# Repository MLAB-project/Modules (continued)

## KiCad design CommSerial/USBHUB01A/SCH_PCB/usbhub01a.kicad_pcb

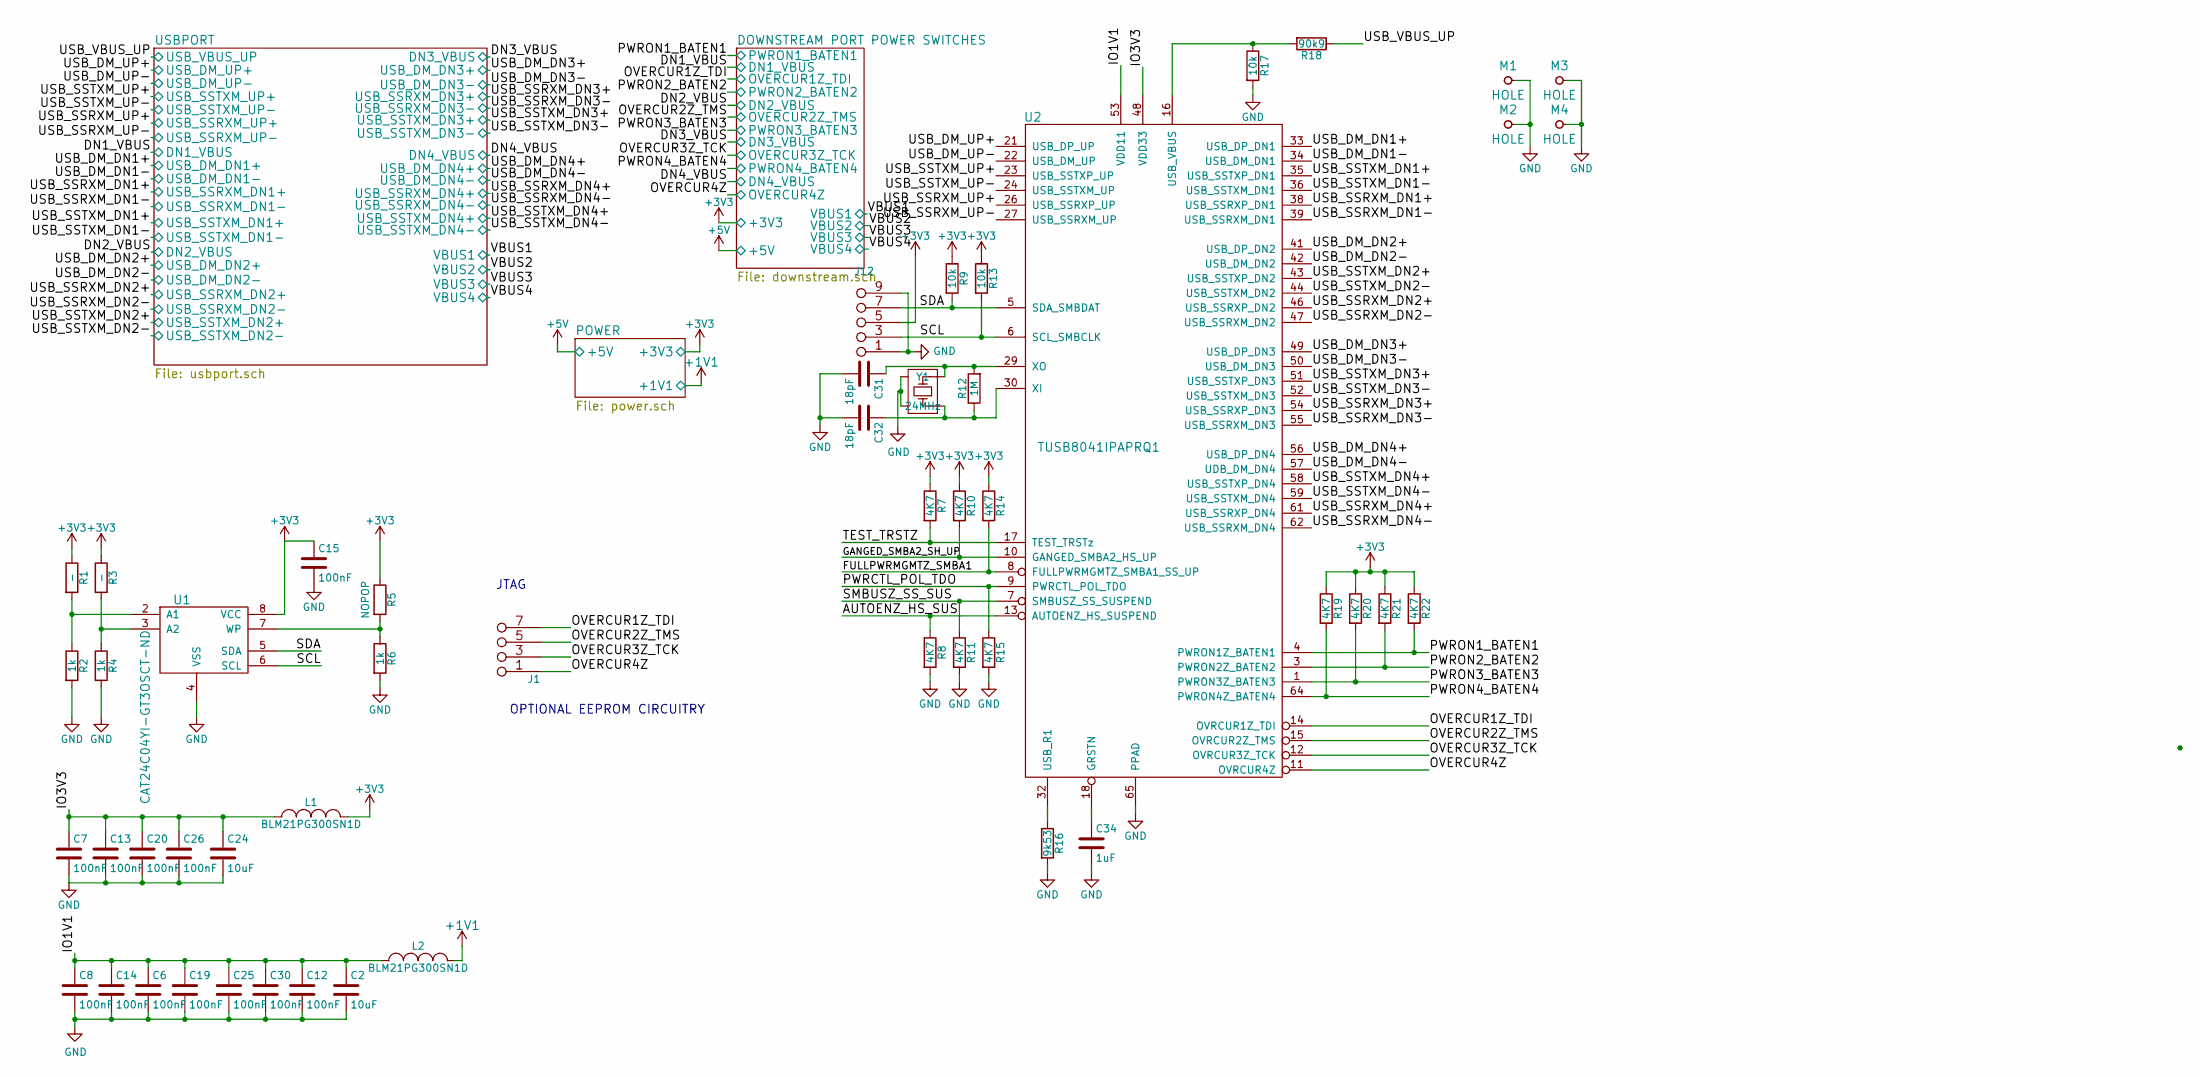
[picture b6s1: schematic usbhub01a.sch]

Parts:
C2, C24: 10uF; SMD-0805
C6, C7, C8, C12, C13, C14, C15, C19, C20, C25, C26, C30: 100nF; SMD-0603
C31, C32: 18pF; SMD-0603
C34: 1uF; SMD-0603
J1: JUMP_2x1; Straight_2x04
J12: JUMP_5X2; Straight_2x05
L1, L2: BLM21PG300SN1D; SMD-0805
M1, M2, M3, M4: HOLE; MountingHole_3mm
R1, R3: -; SMD-0603
R2, R4, R6: 1k; SMD-0603
R5: NOPOP; SMD-0603
R7, R8, R10, R11, R14, R15, R19, R20, R21, R22: 4K7; SMD-0603
R9, R13, R17: 10k; SMD-0603
R12: 1M; SMD-0603
R16: 9k53; SMD-0603
R18: 90k9; SMD-0603
U1: CAT24C04YI-GT3OSCT-ND; TSSOP-8_4.4x3mm_Pitch0.65mm
U2: TUSB8041IPAPRQ1; HTQFP-64_10x10mm_Pitch0.5mm
Y1: 24MHz; NX2016HA

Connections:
+1V1: L2.2; also elsewhere on the board
+3V3: C15.1, J12.5 (6), J12.6, L1.2, R1.1, R3.1, R5.1, R7.1, R9.1, R10.1, R13.1, R14.1, R19.1, R20.1, R21.1, R22.1, U1.8 (VCC); also elsewhere on the board
/AUTOENZ_HS_SUS: R8.1, U2.13 (AUTOENZ_HS_SUSPEND); also elsewhere on the board
/FULLPWRMGMTZ_SMBA1: R14.2, U2.8 (FULLPWRMGMTZ_SMBA1_SS_UP); also elsewhere on the board
/GANGED_SMBA2_SH_UP: R10.2, U2.10 (GANGED_SMBA2_HS_UP); also elsewhere on the board
/IO1V1: C2.1, C6.1, C8.1, C12.1, C14.1, C19.1, C25.1, C30.1, L2.1, U2.19 (VDD11), U2.25 (VDD11), U2.37 (VDD11), U2.45 (VDD11), U2.53 (VDD11), U2.60 (VDD11), U2.63 (VDD11)
/IO3V3: C7.1, C13.1, C20.1, C24.1, C26.1, L1.1, U2.2 (VDD33), U2.20 (VDD33), U2.31 (VDD33), U2.48 (VDD33)
/OVERCUR1Z_TDI: J1.7 (8), J1.8, U2.14 (OVRCUR1Z_TDI); also elsewhere on the board
/OVERCUR2Z_TMS: J1.5, J1.6 (5), U2.15 (OVRCUR2Z_TMS); also elsewhere on the board
/OVERCUR3Z_TCK: J1.3 (4), J1.4, U2.12 (OVRCUR3Z_TCK); also elsewhere on the board
/OVERCUR4Z: J1.1 (2), J1.2, U2.11 (OVRCUR4Z); also elsewhere on the board
/PWRCTL_POL_TDO: R15.1, U2.9 (PWRCTL_POL_TDO); also elsewhere on the board
/PWRON1_BATEN1: R22.2, U2.4 (PWRON1Z_BATEN1); also elsewhere on the board
/PWRON2_BATEN2: R21.2, U2.3 (PWRON2Z_BATEN2); also elsewhere on the board
/PWRON3_BATEN3: R20.2, U2.1 (PWRON3Z_BATEN3); also elsewhere on the board
/PWRON4_BATEN4: R19.2, U2.64 (PWRON4Z_BATEN4); also elsewhere on the board
/SCL: J12.3 (4), J12.4, R13.2, U1.6 (SCL), U2.6 (SCL_SMBCLK)
/SDA: J12.7, J12.8 (7), R9.2, U1.5 (SDA), U2.5 (SDA_SMBDAT)
/SMBUSZ_SS_SUS: R11.1, U2.7 (SMBUSZ_SS_SUSPEND); also elsewhere on the board
/TEST_TRSTZ: R7.2, U2.17 (TEST_TRSTz); also elsewhere on the board
/USB_DM_DN1+: U2.33 (USB_DP_DN1); also elsewhere on the board
/USB_DM_DN1-: U2.34 (USB_DM_DN1); also elsewhere on the board
/USB_DM_DN2+: U2.41 (USB_DP_DN2); also elsewhere on the board
/USB_DM_DN2-: U2.42 (USB_DM_DN2); also elsewhere on the board
/USB_DM_DN3+: U2.49 (USB_DP_DN3); also elsewhere on the board
/USB_DM_DN3-: U2.50 (USB_DM_DN3); also elsewhere on the board
/USB_DM_DN4+: U2.56 (USB_DP_DN4); also elsewhere on the board
/USB_DM_DN4-: U2.57 (UDB_DM_DN4); also elsewhere on the board
/USB_DM_UP+: U2.21 (USB_DP_UP); also elsewhere on the board
/USB_DM_UP-: U2.22 (USB_DM_UP); also elsewhere on the board
/USB_SSRXM_DN1+: U2.38 (USB_SSRXP_DN1); also elsewhere on the board
/USB_SSRXM_DN1-: U2.39 (USB_SSRXM_DN1); also elsewhere on the board
/USB_SSRXM_DN2+: U2.46 (USB_SSRXP_DN2); also elsewhere on the board
/USB_SSRXM_DN2-: U2.47 (USB_SSRXM_DN2); also elsewhere on the board
/USB_SSRXM_DN3+: U2.54 (USB_SSRXP_DN3); also elsewhere on the board
/USB_SSRXM_DN3-: U2.55 (USB_SSRXM_DN3); also elsewhere on the board
/USB_SSRXM_DN4+: U2.61 (USB_SSRXP_DN4); also elsewhere on the board
/USB_SSRXM_DN4-: U2.62 (USB_SSRXM_DN4); also elsewhere on the board
/USB_SSRXM_UP+: U2.26 (USB_SSRXP_UP); also elsewhere on the board
/USB_SSRXM_UP-: U2.27 (USB_SSRXM_UP); also elsewhere on the board
/USB_SSTXM_DN1+: U2.35 (USB_SSTXP_DN1); also elsewhere on the board
/USB_SSTXM_DN1-: U2.36 (USB_SSTXM_DN1); also elsewhere on the board
/USB_SSTXM_DN2+: U2.43 (USB_SSTXP_DN2); also elsewhere on the board
/USB_SSTXM_DN2-: U2.44 (USB_SSTXM_DN2); also elsewhere on the board
/USB_SSTXM_DN3+: U2.51 (USB_SSTXP_DN3); also elsewhere on the board
/USB_SSTXM_DN3-: U2.52 (USB_SSTXM_DN3); also elsewhere on the board
/USB_SSTXM_DN4+: U2.58 (USB_SSTXP_DN4); also elsewhere on the board
/USB_SSTXM_DN4-: U2.59 (USB_SSTXM_DN4); also elsewhere on the board
/USB_SSTXM_UP+: U2.23 (USB_SSTXP_UP); also elsewhere on the board
/USB_SSTXM_UP-: U2.24 (USB_SSTXM_UP); also elsewhere on the board
/USB_VBUS_UP: R18.1; also elsewhere on the board
GND: C2.2, C6.2, C7.2, C8.2, C12.2, C13.2, C14.2, C15.2, C19.2, C20.2, C24.2, C25.2, C26.2, C30.2, C31.2, C32.2, C34.2, J12.1 (2), J12.2, J12.9 (10), J12.10, M1.1, M2.1, M3.1, M4.1, R2.2, R4.2, R6.2, R8.2, R11.2, R15.2, R16.2, R17.2, U1.4 (VSS), U2.65 (PPAD), Y1.2, Y1.4; also elsewhere on the board
unnamed: C31.1, R12.2, U2.29 (XO), Y1.3
unnamed: C32.1, R12.1, U2.30 (XI), Y1.1
unnamed: C34.1, U2.18 (GRSTN)
unnamed: R1.2, R2.1, U1.2 (A1)
unnamed: R3.2, R4.1, U1.3 (A2)
unnamed: R5.2, R6.1, U1.7 (WP)
unnamed: R16.1, U2.32 (USB_R1)
unnamed: R17.1, R18.2, U2.16 (USB_VBUS)

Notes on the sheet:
OPTIONAL EEPROM CIRCUITRY
JTAG

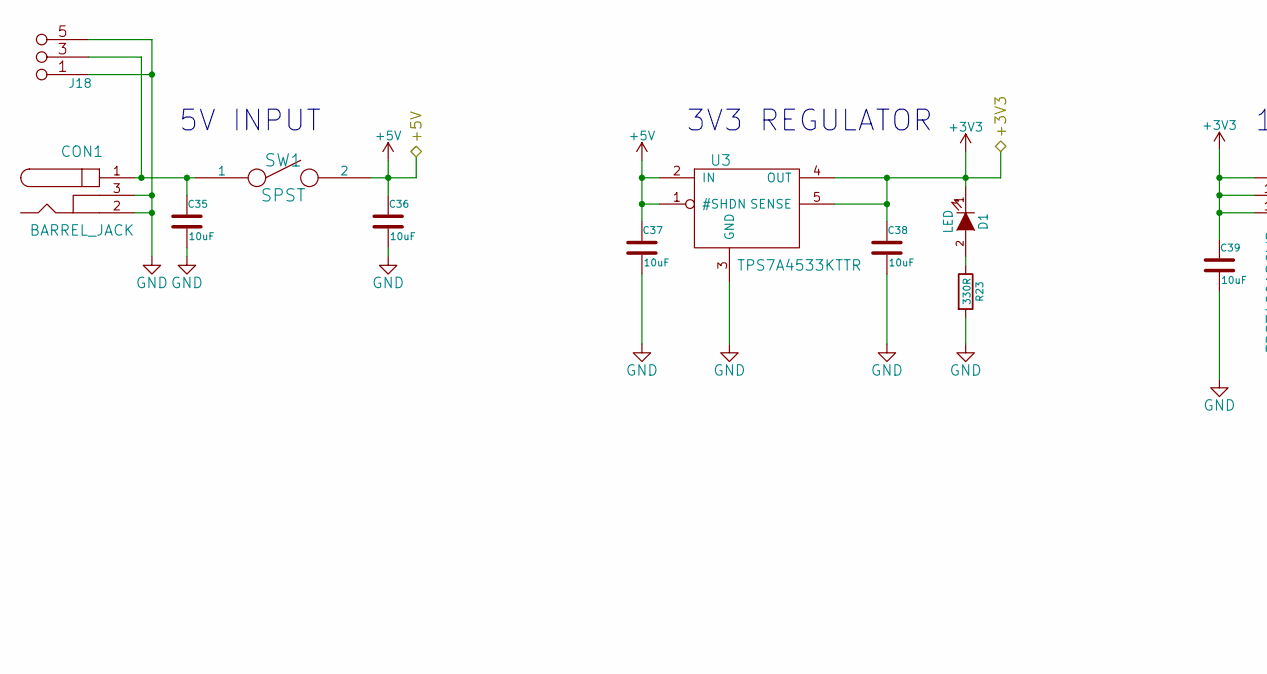
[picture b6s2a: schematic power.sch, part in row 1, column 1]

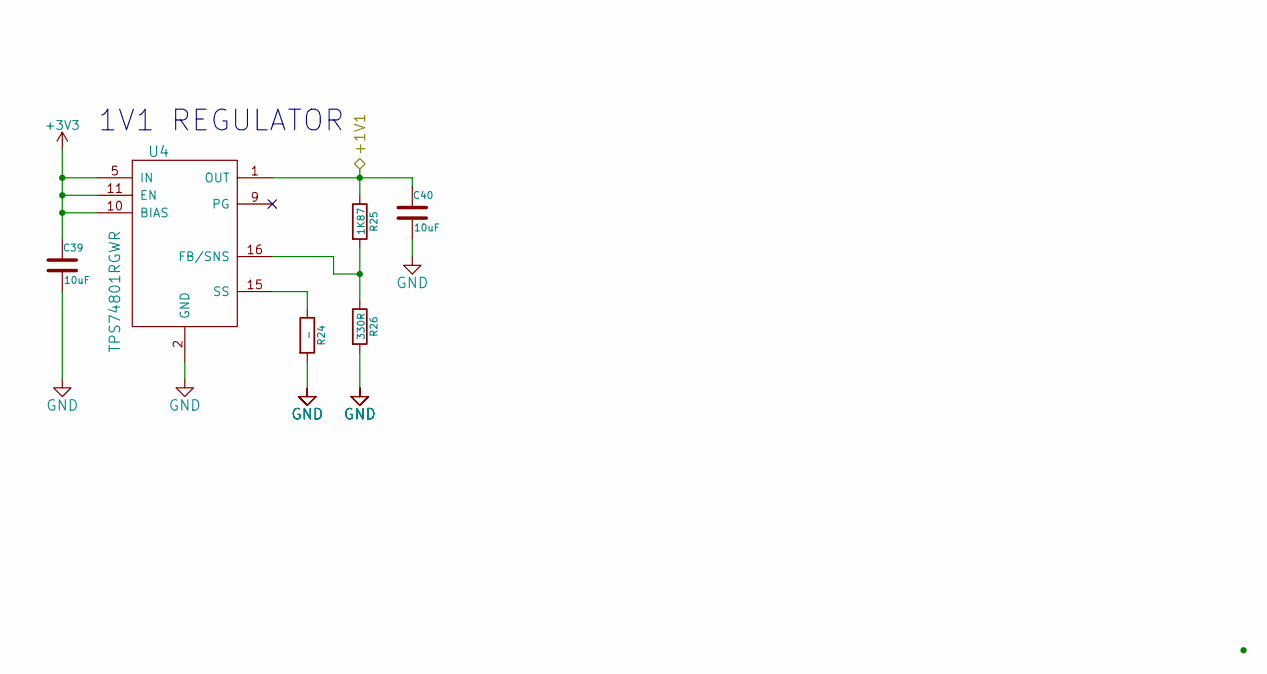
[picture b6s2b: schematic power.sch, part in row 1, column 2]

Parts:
C35, C36, C37, C38, C39, C40: 10uF; SMD-0805
CON1: BARREL_JACK; DC2,1MM
D1: LED; LED_1206
J18: JUMP_3X2; Straight_2x03
R23, R26: 330R; SMD-0603
R24: -; SMD-0603
R25: 1K87; SMD-0603
SW1: SPST; Prepinaci_3A_SL19121
U3: TPS7A4533KTTR; TO-263-5
U4: TPS74801RGWR; QFN-20-1EP_5x5mm_Pitch0.65mm

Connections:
+1V1: C40.1, R25.1, U4.1 (OUT), U4.18 (OUT), U4.19 (OUT), U4.20 (OUT); also elsewhere on the board
+3V3: C38.1, C39.1, D1.1 (K), U3.4 (OUT), U3.5 (SENSE), U4.5 (IN), U4.6 (IN), U4.7 (IN), U4.8 (IN), U4.10 (BIAS), U4.11 (EN); also elsewhere on the board
+5V: C36.1, C37.1, SW1.2, U3.1 (#SHDN), U3.2 (IN); also elsewhere on the board
GND: C35.2, C36.2, C37.2, C38.2, C39.2, C40.2, CON1.2, CON1.3, J18.1 (2), J18.2, J18.5 (6), J18.6, R23.2, R24.2, R26.2, U3.3 (GND), U3.6 (GND), U4.2 (GND), U4.3 (GND), U4.4 (GND), U4.12 (GND), U4.13 (GND), U4.14 (GND), U4.21; also elsewhere on the board
unnamed: C35.1, CON1.1, J18.3 (4), J18.4, SW1.1
unnamed: D1.2 (A), R23.1
unnamed: R24.1, U4.15 (SS)
unnamed: R25.2, R26.1, U4.16 (FB/SNS)

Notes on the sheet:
5V INPUT
3V3 REGULATOR
1V1 REGULATOR

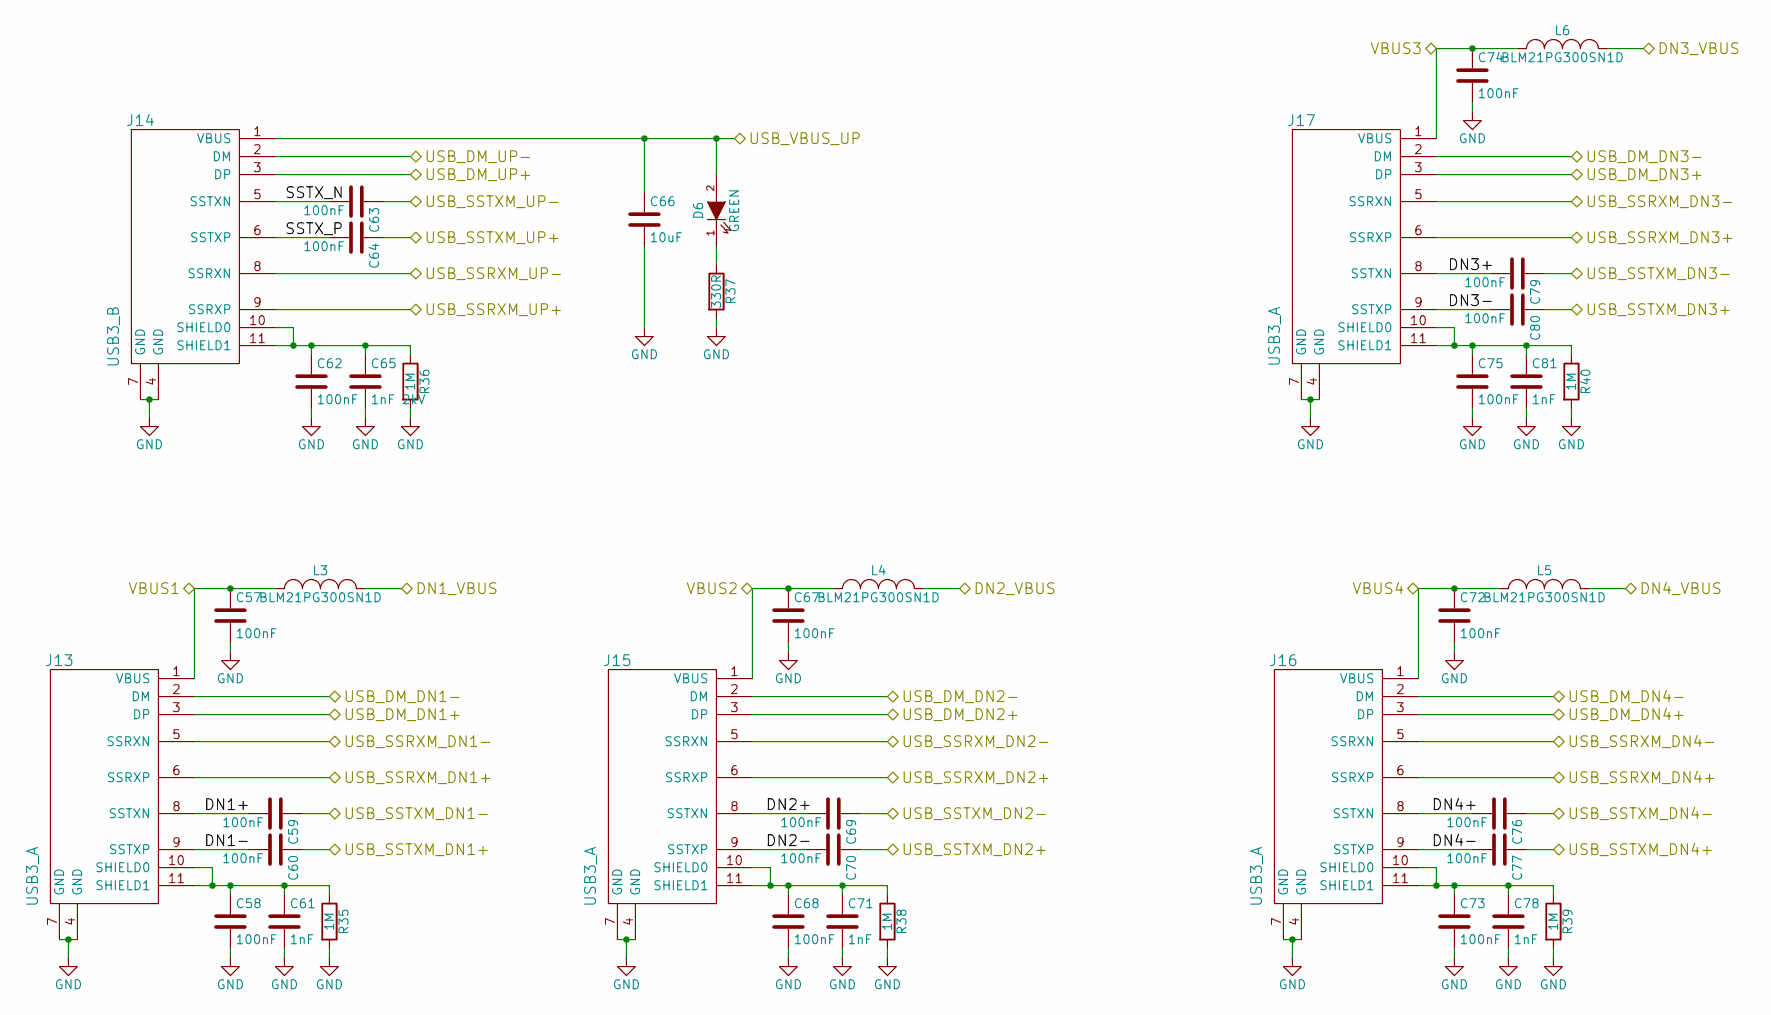
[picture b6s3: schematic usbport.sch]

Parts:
C57, C58, C59, C60, C62, C63, C64, C67, C68, C69, C70, C72, C73, C74, C75, C76, C77, C79, C80: 100nF; SMD-0603
C61, C71, C78, C81: 1nF; SMD-0603
C65: 1nF 2kV; SMD-0603
C66: 10uF; SMD-0603
D6: GREEN; LED_1206
J13, J15, J16, J17: USB3_A; USB3_0_A
J14: USB3_B; USB3_0_B
L3, L4, L5, L6: BLM21PG300SN1D; SMD-0805
R35, R36, R38, R39, R40: 1M; SMD-0603
R37: 330R; SMD-0603

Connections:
/DN1_VBUS: L3.2; also elsewhere on the board
/DN2_VBUS: L4.2; also elsewhere on the board
/DN3_VBUS: L6.2; also elsewhere on the board
/DN4_VBUS: L5.2; also elsewhere on the board
/USBPORT/DN1+: C59.2, J13.8 (SSTXN)
/USBPORT/DN1-: C60.2, J13.9 (SSTXP)
/USBPORT/DN2+: C69.2, J15.8 (SSTXN)
/USBPORT/DN2-: C70.2, J15.9 (SSTXP)
/USBPORT/DN3+: C79.2, J17.8 (SSTXN)
/USBPORT/DN3-: C80.2, J17.9 (SSTXP)
/USBPORT/DN4+: C76.2, J16.8 (SSTXN)
/USBPORT/DN4-: C77.2, J16.9 (SSTXP)
/USBPORT/SSTX_N: C63.2, J14.5 (SSTXN)
/USBPORT/SSTX_P: C64.2, J14.6 (SSTXP)
/USB_DM_DN1+: J13.3 (DP); also elsewhere on the board
/USB_DM_DN1-: J13.2 (DM); also elsewhere on the board
/USB_DM_DN2+: J15.3 (DP); also elsewhere on the board
/USB_DM_DN2-: J15.2 (DM); also elsewhere on the board
/USB_DM_DN3+: J17.3 (DP); also elsewhere on the board
/USB_DM_DN3-: J17.2 (DM); also elsewhere on the board
/USB_DM_DN4+: J16.3 (DP); also elsewhere on the board
/USB_DM_DN4-: J16.2 (DM); also elsewhere on the board
/USB_DM_UP+: J14.3 (DP); also elsewhere on the board
/USB_DM_UP-: J14.2 (DM); also elsewhere on the board
/USB_SSRXM_DN1+: J13.6 (SSRXP); also elsewhere on the board
/USB_SSRXM_DN1-: J13.5 (SSRXN); also elsewhere on the board
/USB_SSRXM_DN2+: J15.6 (SSRXP); also elsewhere on the board
/USB_SSRXM_DN2-: J15.5 (SSRXN); also elsewhere on the board
/USB_SSRXM_DN3+: J17.6 (SSRXP); also elsewhere on the board
/USB_SSRXM_DN3-: J17.5 (SSRXN); also elsewhere on the board
/USB_SSRXM_DN4+: J16.6 (SSRXP); also elsewhere on the board
/USB_SSRXM_DN4-: J16.5 (SSRXN); also elsewhere on the board
/USB_SSRXM_UP+: J14.9 (SSRXP); also elsewhere on the board
/USB_SSRXM_UP-: J14.8 (SSRXN); also elsewhere on the board
/USB_SSTXM_DN1+: C60.1; also elsewhere on the board
/USB_SSTXM_DN1-: C59.1; also elsewhere on the board
/USB_SSTXM_DN2+: C70.1; also elsewhere on the board
/USB_SSTXM_DN2-: C69.1; also elsewhere on the board
/USB_SSTXM_DN3+: C80.1; also elsewhere on the board
/USB_SSTXM_DN3-: C79.1; also elsewhere on the board
/USB_SSTXM_DN4+: C77.1; also elsewhere on the board
/USB_SSTXM_DN4-: C76.1; also elsewhere on the board
/USB_SSTXM_UP+: C64.1; also elsewhere on the board
/USB_SSTXM_UP-: C63.1; also elsewhere on the board
/USB_VBUS_UP: C66.1, D6.2 (A), J14.1 (VBUS); also elsewhere on the board
/VBUS1: C57.1, J13.1 (VBUS), L3.1; also elsewhere on the board
/VBUS2: C67.1, J15.1 (VBUS), L4.1; also elsewhere on the board
/VBUS3: C74.1, J17.1 (VBUS), L6.1; also elsewhere on the board
/VBUS4: C72.1, J16.1 (VBUS), L5.1; also elsewhere on the board
GND: C57.2, C58.2, C61.2, C62.2, C65.2, C66.2, C67.2, C68.2, C71.2, C72.2, C73.2, C74.2, C75.2, C78.2, C81.2, J13.4 (GND), J13.7 (GND), J14.4 (GND), J14.7 (GND), J15.4 (GND), J15.7 (GND), J16.4 (GND), J16.7 (GND), J17.4 (GND), J17.7 (GND), R35.2, R36.2, R37.2, R38.2, R39.2, R40.2; also elsewhere on the board
unnamed: C58.1, C61.1, J13.10 (SHIELD0), J13.11 (SHIELD1), R35.1
unnamed: C62.1, C65.1, J14.10 (SHIELD0), J14.11 (SHIELD1), R36.1
unnamed: C68.1, C71.1, J15.10 (SHIELD0), J15.11 (SHIELD1), R38.1
unnamed: C73.1, C78.1, J16.10 (SHIELD0), J16.11 (SHIELD1), R39.1
unnamed: C75.1, C81.1, J17.10 (SHIELD0), J17.11 (SHIELD1), R40.1
unnamed: D6.1 (K), R37.1

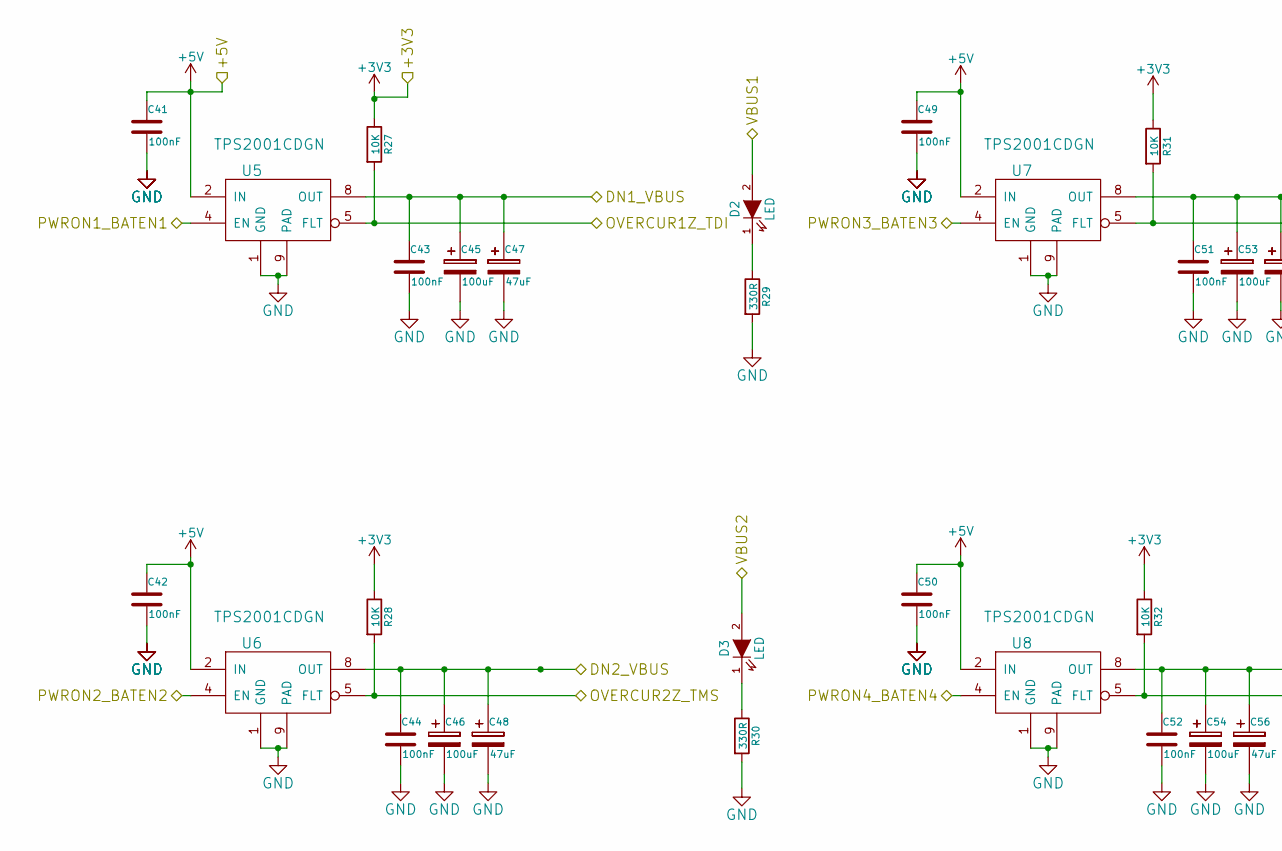
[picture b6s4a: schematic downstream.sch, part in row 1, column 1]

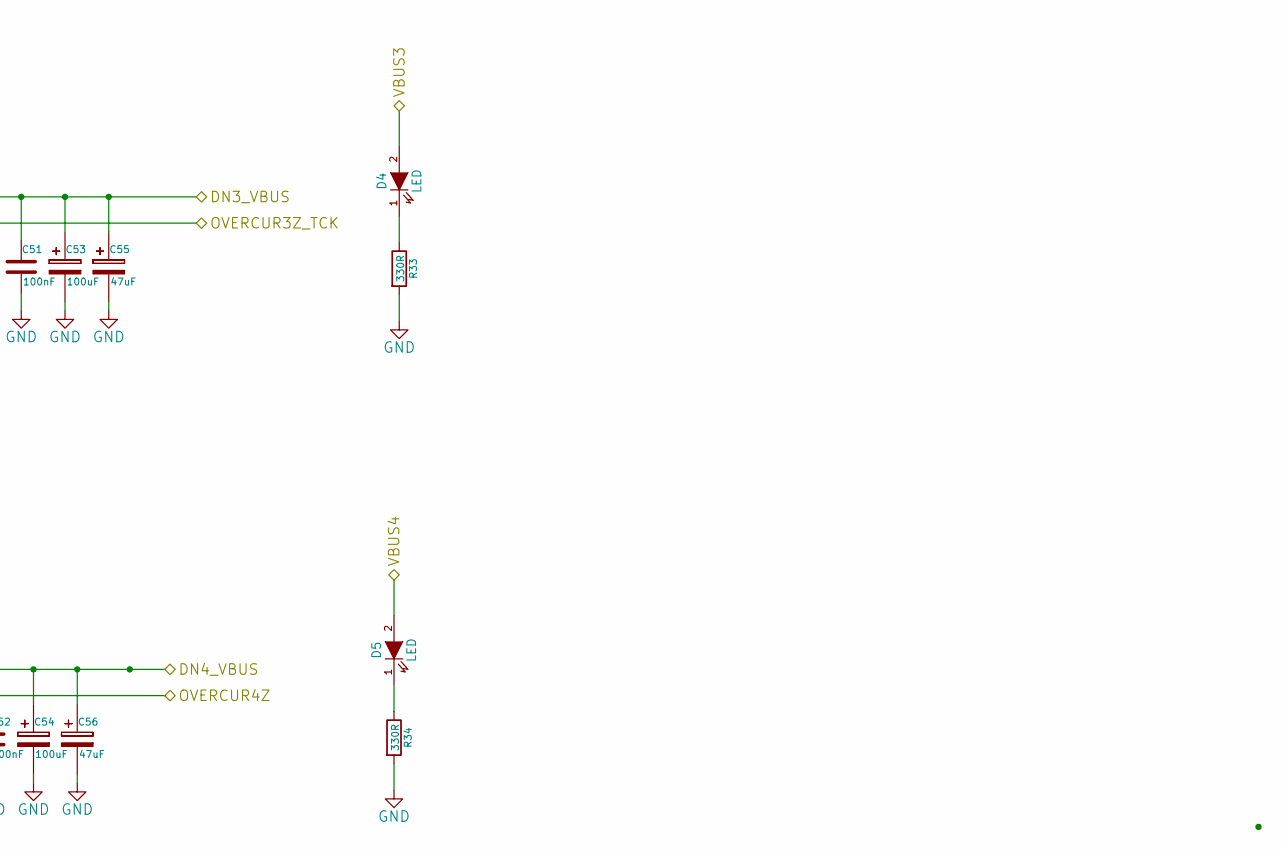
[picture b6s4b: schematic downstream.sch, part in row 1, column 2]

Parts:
C41, C42, C43, C44, C49, C50, C51, C52: 100nF; SMD-0603
C45, C46, C53, C54: 100uF; TantalC_SizeD_Reflow
C47, C48, C55, C56: 47uF; TantalC_SizeC_Reflow
D2, D3, D4, D5: LED; LED_1206
R27, R28, R31, R32: 10K; SMD-0603
R29, R30, R33, R34: 330R; SMD-0603
U5, U6, U7, U8: TPS2001CDGN; MSOP-8-1EP_3x3mm_Pitch0.65mm

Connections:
+3V3: R27.1, R28.1, R31.1, R32.1; also elsewhere on the board
+5V: C41.1, C42.1, C49.1, C50.1, U5.2 (IN), U5.3 (IN), U6.2 (IN), U6.3 (IN), U7.2 (IN), U7.3 (IN), U8.2 (IN), U8.3 (IN); also elsewhere on the board
/DN1_VBUS: C43.1, C45.1, C47.1, U5.6 (OUT), U5.7 (OUT), U5.8 (OUT); also elsewhere on the board
/DN2_VBUS: C44.1, C46.1, C48.1, U6.6 (OUT), U6.7 (OUT), U6.8 (OUT); also elsewhere on the board
/DN3_VBUS: C51.1, C53.1, C55.1, U7.6 (OUT), U7.7 (OUT), U7.8 (OUT); also elsewhere on the board
/DN4_VBUS: C52.1, C54.1, C56.1, U8.6 (OUT), U8.7 (OUT), U8.8 (OUT); also elsewhere on the board
/OVERCUR1Z_TDI: R27.2, U5.5 (FLT); also elsewhere on the board
/OVERCUR2Z_TMS: R28.2, U6.5 (FLT); also elsewhere on the board
/OVERCUR3Z_TCK: R31.2, U7.5 (FLT); also elsewhere on the board
/OVERCUR4Z: R32.2, U8.5 (FLT); also elsewhere on the board
/PWRON1_BATEN1: U5.4 (EN); also elsewhere on the board
/PWRON2_BATEN2: U6.4 (EN); also elsewhere on the board
/PWRON3_BATEN3: U7.4 (EN); also elsewhere on the board
/PWRON4_BATEN4: U8.4 (EN); also elsewhere on the board
/VBUS1: D2.2 (A); also elsewhere on the board
/VBUS2: D3.2 (A); also elsewhere on the board
/VBUS3: D4.2 (A); also elsewhere on the board
/VBUS4: D5.2 (A); also elsewhere on the board
GND: C41.2, C42.2, C43.2, C44.2, C45.2, C46.2, C47.2, C48.2, C49.2, C50.2, C51.2, C52.2, C53.2, C54.2, C55.2, C56.2, R29.2, R30.2, R33.2, R34.2, U5.1 (GND), U5.9 (PAD), U6.1 (GND), U6.9 (PAD), U7.1 (GND), U7.9 (PAD), U8.1 (GND), U8.9 (PAD); also elsewhere on the board
unnamed: D2.1 (K), R29.1
unnamed: D3.1 (K), R30.1
unnamed: D4.1 (K), R33.1
unnamed: D5.1 (K), R34.1

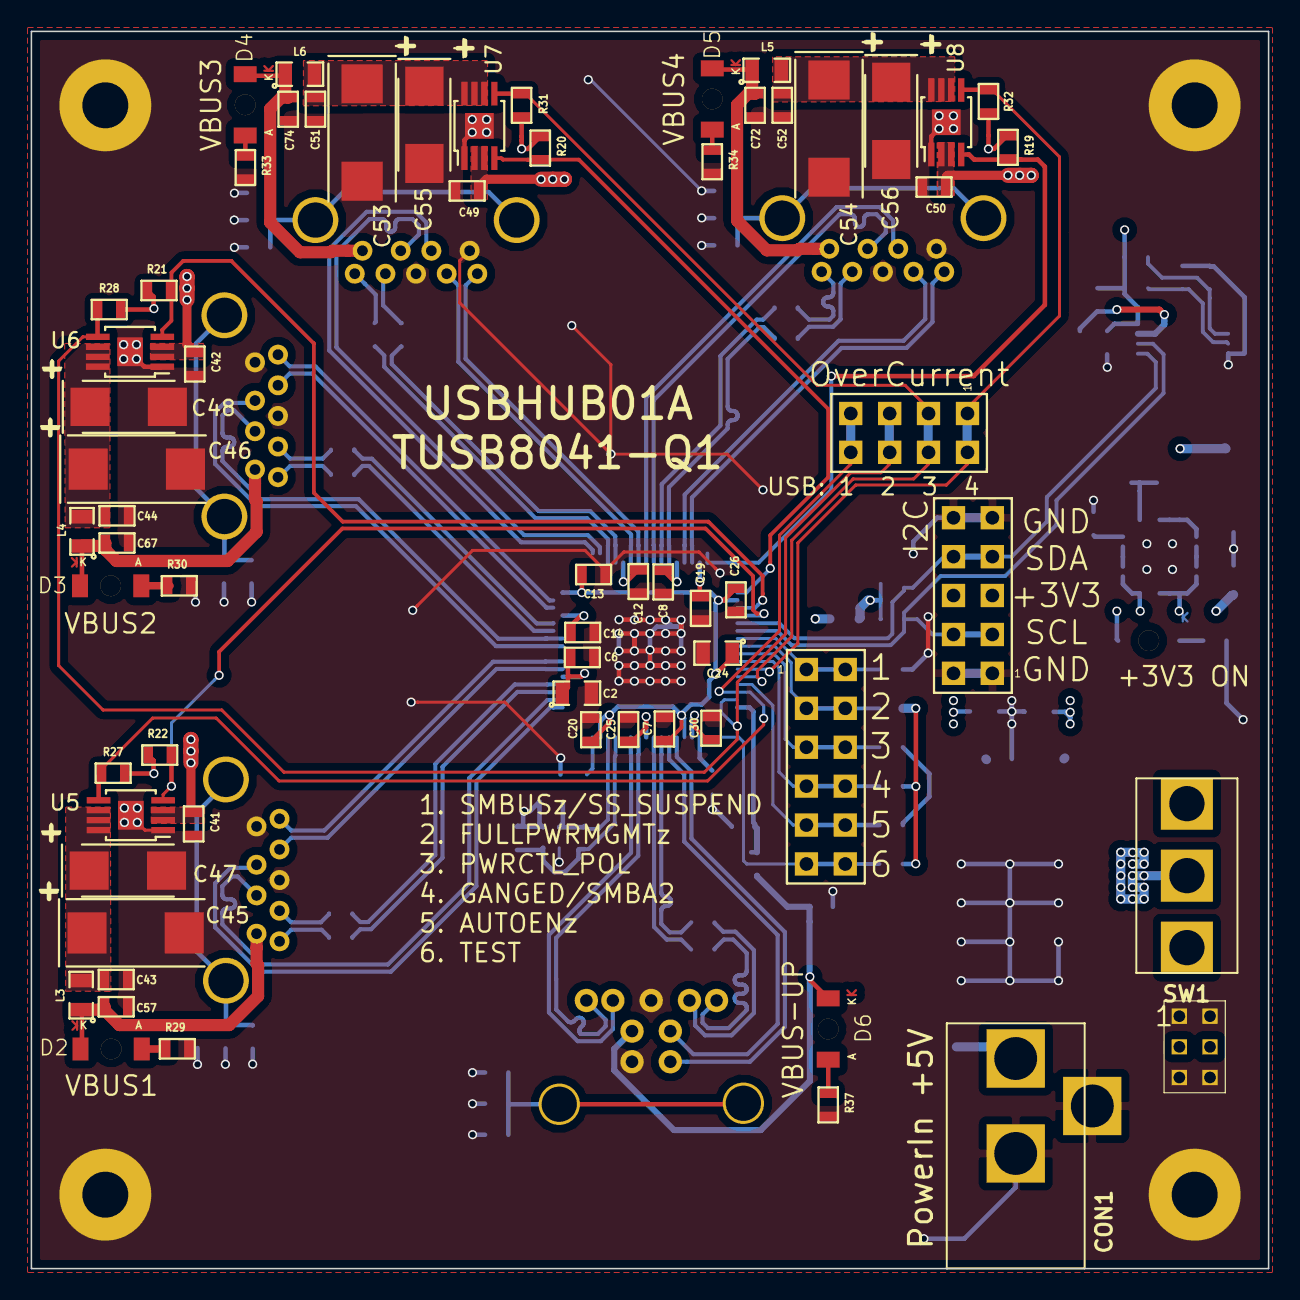
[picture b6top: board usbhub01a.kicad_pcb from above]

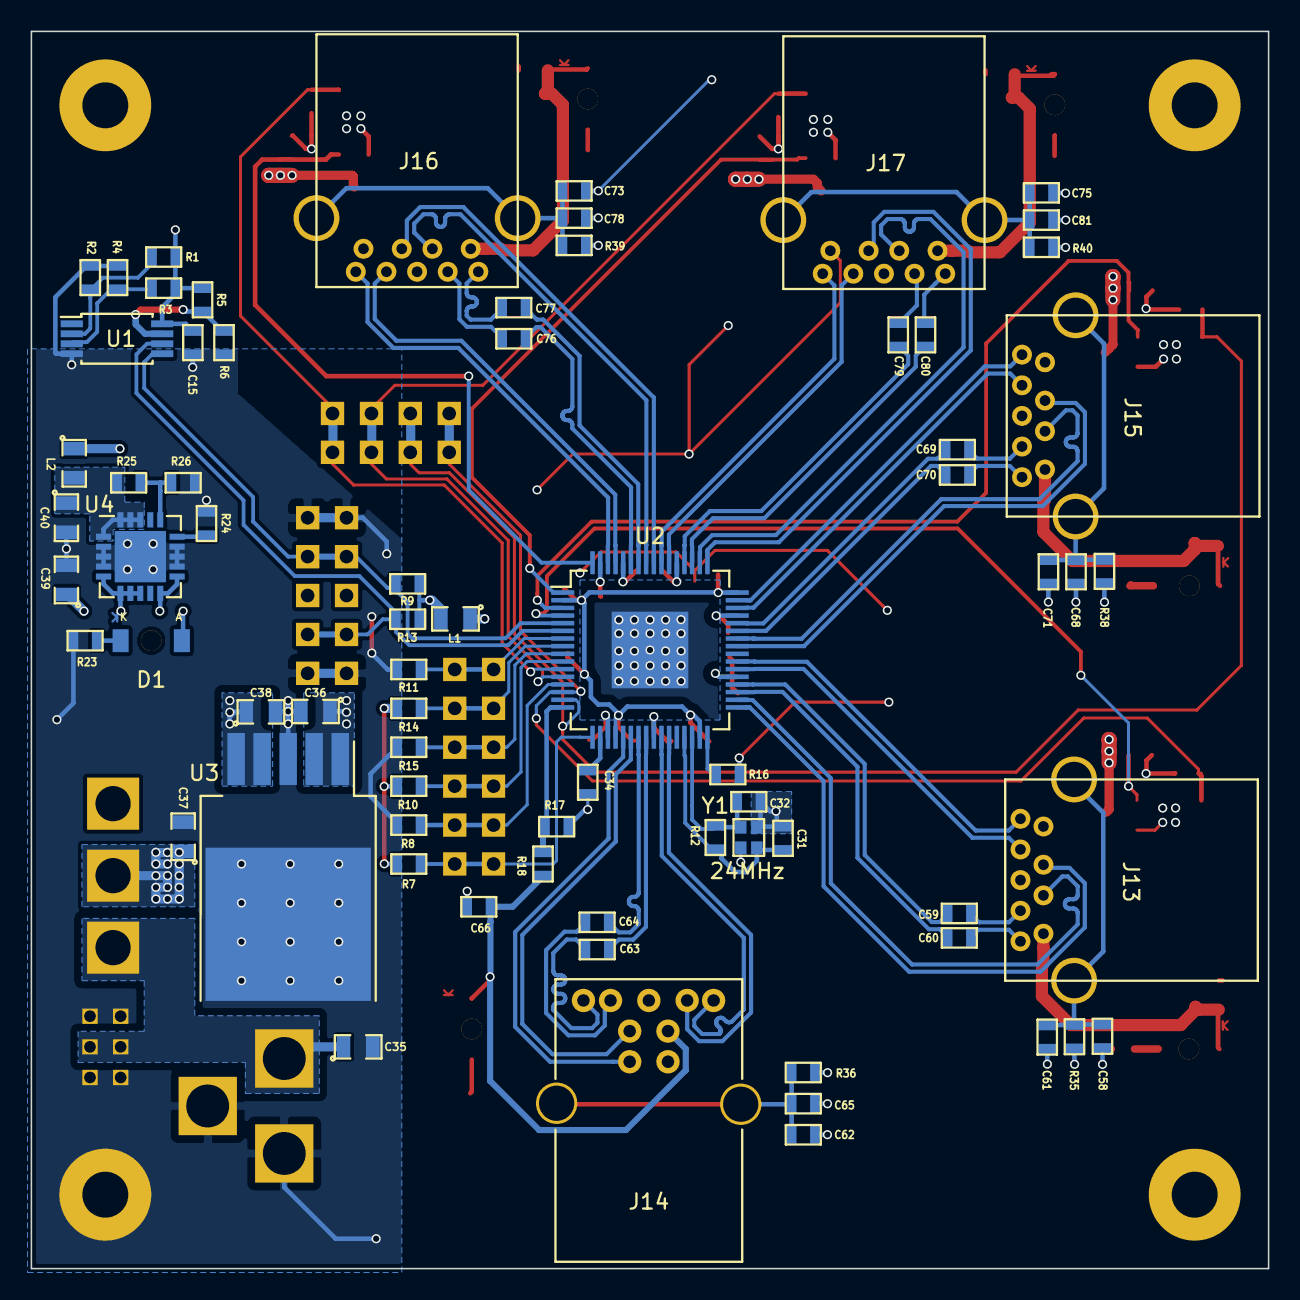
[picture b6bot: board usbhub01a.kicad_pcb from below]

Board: 4 copper layers, 80.8 x 80.8 mm, 140 parts (71 on the bottom side), 93 nets.

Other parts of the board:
J2: Test & Misc Signals; Straight_2x06

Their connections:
/AUTOENZ_HS_SUS: J2.9, J2.10; also elsewhere on the board
/FULLPWRMGMTZ_SMBA1: J2.3, J2.4; also elsewhere on the board
/GANGED_SMBA2_SH_UP: J2.7, J2.8; also elsewhere on the board
/PWRCTL_POL_TDO: J2.5, J2.6; also elsewhere on the board
/SMBUSZ_SS_SUS: J2.1, J2.2; also elsewhere on the board
/TEST_TRSTZ: J2.11, J2.12; also elsewhere on the board

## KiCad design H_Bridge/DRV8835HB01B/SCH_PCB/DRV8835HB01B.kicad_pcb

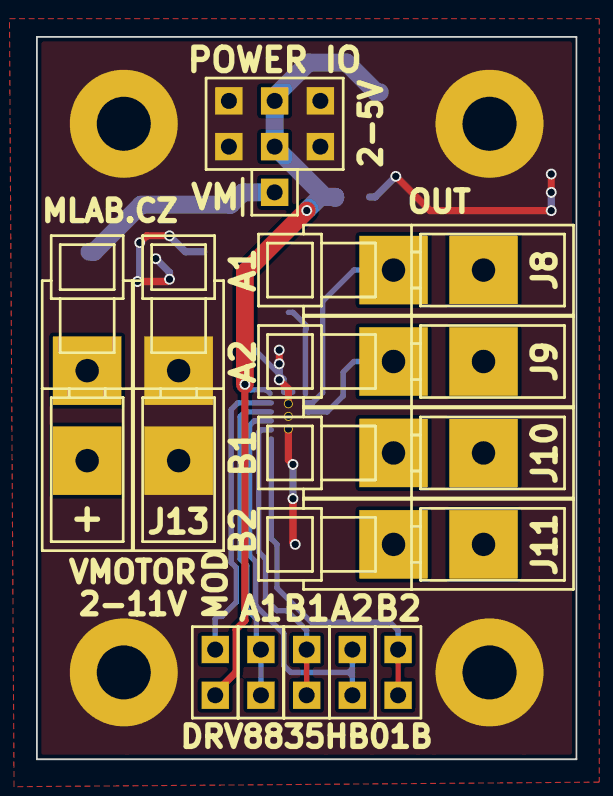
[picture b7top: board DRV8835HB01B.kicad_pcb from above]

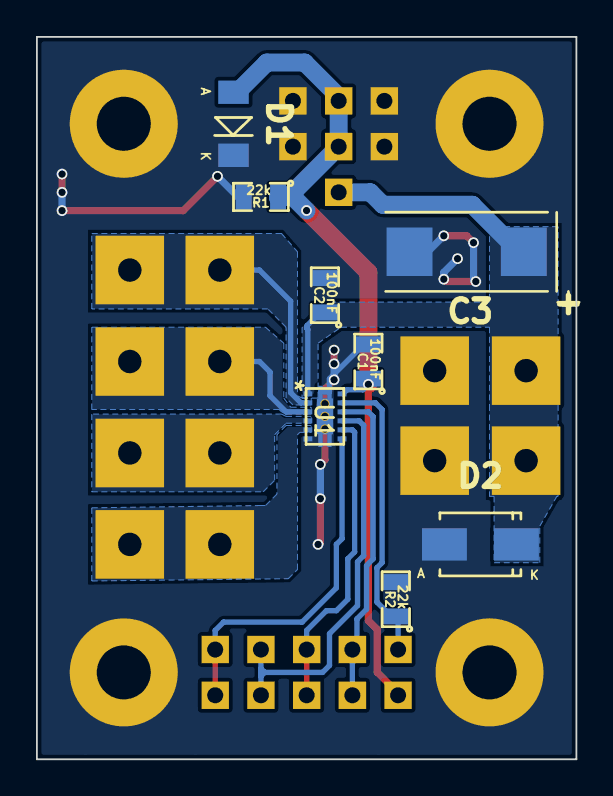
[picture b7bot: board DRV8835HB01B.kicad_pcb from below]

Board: 2 copper layers, 30.0 x 40.1 mm, 25 parts (8 on the bottom side), 12 nets.

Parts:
C1, C2: 100nF; SMD-0805
C3: 100uF; TantalC_SizeD_Reflow
D1: BZV55C-5,6V; Diode-MiniMELF_Standard
D2: M4; Diode-SMA_Standard
J1: JUMP_3X2; Straight_2x03
J2: CONN1_1; Straight_1x01
J3, J4, J5, J6: JUMP_2x1; Straight_2x01
J7: JUMP2_2x1; Straight_2x01
J8, J9, J10, J11, J12, J13: WAGO256
M1, M2, M3, M4: HOLE; MountingHole_3mm
R1, R2: 22k; SMD-0805
U1: DRV8835; WSON-12

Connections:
/AIN1: J3.1, J3.2, U1.10
/AIN2: J4.1, J4.2, U1.9
/AOUT1: J8.1, U1.2
/AOUT2: J9.1, U1.3
/BIN1: J5.1, J5.2, U1.8
/BIN2: J6.1, J6.2, U1.7
/BOUT1: J10.1, U1.4
/BOUT2: J11.1, U1.5
/VM: C2.1, C3.1, D2.2, J2.1, J12.1, U1.1
GND: C1.2, C2.2, C3.2, D1.2, D2.1, J1.1, J1.2, J1.5, J1.6, J13.1, M1.1, M2.1, M3.1, M4.1, R1.2, R2.2, U1.6
unnamed: J7.1, R2.1, U1.11
VCC: C1.1, D1.1, J1.3, J1.4, J7.2, R1.1, U1.12

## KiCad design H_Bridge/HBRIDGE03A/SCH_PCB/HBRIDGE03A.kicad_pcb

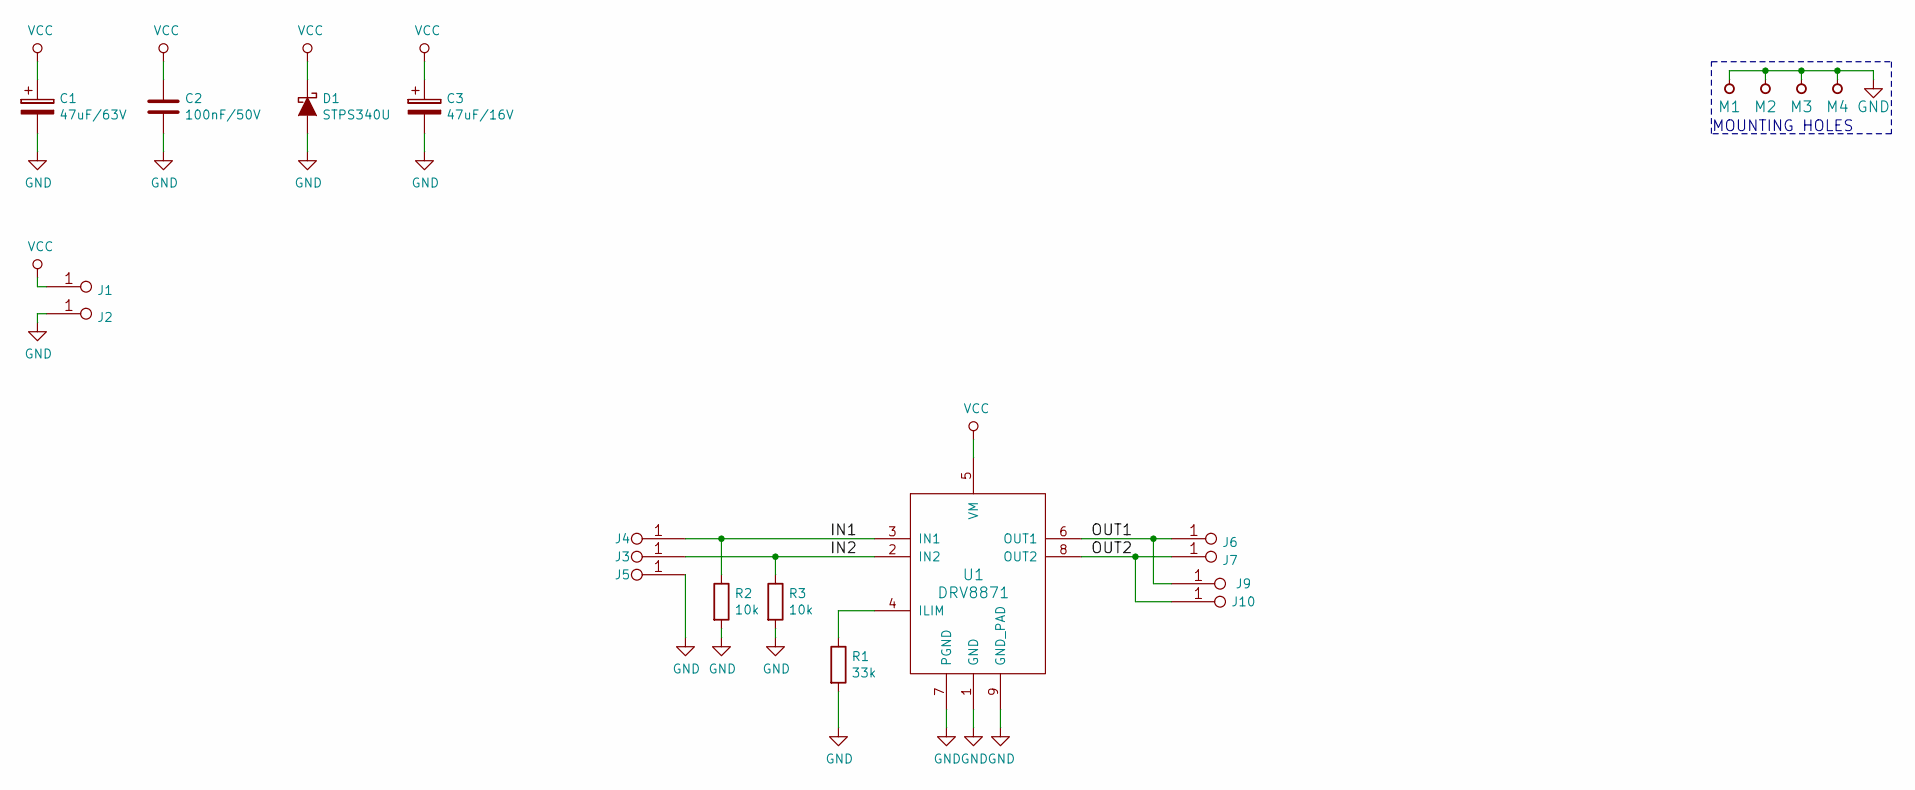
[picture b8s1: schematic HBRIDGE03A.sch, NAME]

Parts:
C1: 47uF/63V; C_Radial_D6.3_L11.2_P2.5
C2: 100nF/50V; SMD-0805
C3: 47uF/16V; TantalC_SizeC_Reflow
D1: STPS340U; Diode-SMB_Standard
J1, J2, J6, J7: CONN1_1; WAGO256
J3, J4, J5, J9, J10: JUMP_2x1; Straight_2x01
M1, M2, M3, M4: HOLE; MountingHole_3mm
R1: 33k; SMD-0805
R2, R3: 10k; SMD-0805
U1: DRV8871; HSOP-8

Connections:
/IN1: J3.1, J3.2, R2.1, U1.3 (IN1)
/IN2: J4.1, J4.2, R3.1, U1.2 (IN2)
/OUT1: J6.1, J9.1, J9.2, U1.6 (OUT1)
/OUT2: J7.1, J10.1, J10.2, U1.8 (OUT2)
GND: C1.2, C2.2, C3.2, D1.2 (A), J2.1, J5.1, J5.2, M1.1, M2.1, M3.1, M4.1, R1.2, R2.2, R3.2, U1.1 (GND), U1.7 (PGND), U1.9 (GND_PAD)
unnamed: R1.1, U1.4 (ILIM)
VCC: C1.1, C2.1, C3.1, D1.1 (K), J1.1, U1.5 (VM)

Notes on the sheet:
MOUNTING HOLES
